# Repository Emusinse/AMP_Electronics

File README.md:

# AMP_Electronics
Custom speaker amplifier using TPA3126 IC

## Aim
This project aims to create a Class D speaker amplifier capabile of driving a set of 50W speakers. This is a personal prokect to replace a cheap 100W amps for a set of desk speakers,
Micca MB42.

## Requirements
- 2 x 50W outputs
- small form factor, smaller than 100mm x 100mm, allows cheaper PCBs
- Volume control, power switch
- AUX in, potentially RCA
- spring termiinal output
- Class D amplifier

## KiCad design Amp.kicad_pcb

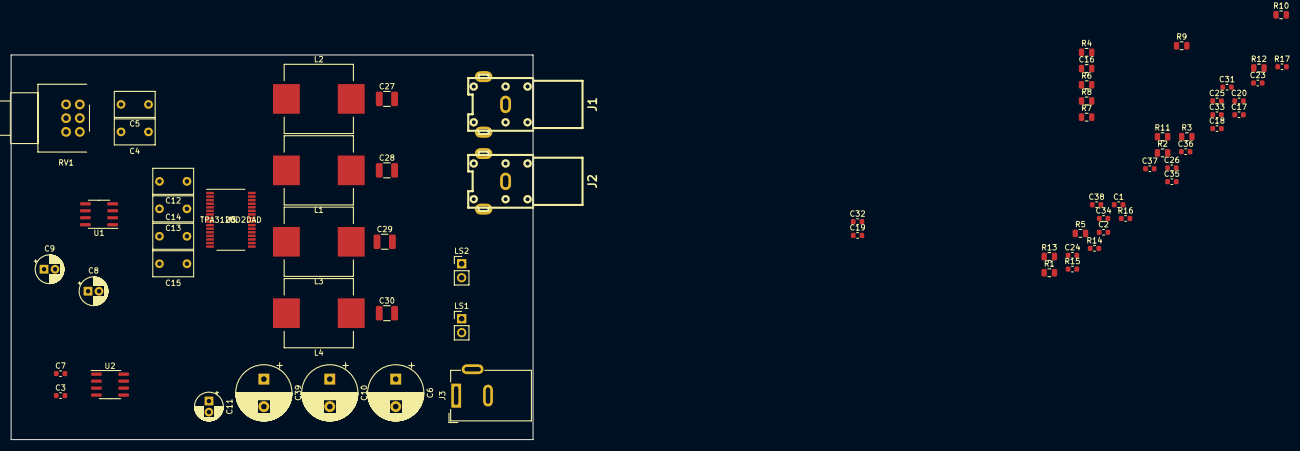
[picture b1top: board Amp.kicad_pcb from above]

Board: 2 copper layers, 95.0 x 70.0 mm, 67 parts (0 on the bottom side), 44 nets, no tracks yet.

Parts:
C1, C7, C19, C20: 100n; C_0603_1608Metric
C2, C17, C18, C31, C32, C33, C34: 1n; C_0603_1608Metric
C3: 330n; C_0603_1608Metric
C4, C5, C12, C13, C14, C15: 1u; C_Rect_L7.2mm_W4.5mm_P5.00mm_FKS2_FKP2_MKS2_MKP2
C6, C10, C39: 220uf; CP_Radial_D10.0mm_P5.00mm
C8, C9, C11: 10u; CP_Radial_D5.0mm_P2.00mm
C16: 1u; C_0805_2012Metric
C23, C24, C25, C26: 220n; C_0603_1608Metric
C27, C28, C29, C30: 680n; C_1210_3225Metric
C35, C36, C37, C38: 10n; C_0603_1608Metric
J1, J2: Conn_Coaxial; rca
J3: Barrel_Jack; BarrelJack_Wuerth_6941xx301002
L1, L2, L3, L4: 10u; L_Wuerth_WE-PD-Typ-LS_Handsoldering
LS1, LS2: L; PinHeader_1x02_P2.54mm_Vertical
R1, R2, R7, R8: 1k; R_0805_2012Metric
R3, R4, R9, R10: 47k; R_0805_2012Metric
R5, R6: 680; R_0805_2012Metric
R11, R13: 100k; R_0805_2012Metric
R12: 20k; R_0805_2012Metric
R14, R15, R16, R17: 10R; R_0603_1608Metric
RV1: R_POT_Dual-Device; Potentiometer_Bourns_PTD90_Double
U1: NE5532; SOIC-8_3.9x4.9mm_P1.27mm
U2: MC78L12_SO8; SOIC-8_3.9x4.9mm_P1.27mm
U3: TPA3126D2DAD

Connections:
+12V: C1.2, C2.1, C7.1, U1.8, U2.1
/LIN: C14.2, R10.2
/RIN: C12.2, R9.2
GNDA: C1.1, C2.2, C8.2, C9.2, C13.2, C15.2, C27.2, C28.1, C29.2, C30.1, C31.2, C32.1, C33.2, C34.1, J1.2, J2.2, R3.1, R4.1, R14.2, R15.1, R16.2, R17.1, RV1.3, RV1.6, U1.4
GNDD: C3.2, C6.2, C7.2, C10.2, C11.2, C16.2, C17.2, C18.2, C19.2, C20.2, C39.2, J3.2, R12.2, R13.1, U2.2, U2.3, U2.6, U2.7, U3.9, U3.13, U3.14, U3.15, U3.16, U3.22, U3.25, U3.28
unnamed: C4.1, R1.2
unnamed: C4.2, RV1.2
unnamed: C5.1, R2.2
unnamed: C5.2, RV1.5
unnamed: C8.1, R5.1
unnamed: C9.1, R6.1
unnamed: C6.1, C10.1, C11.1, C39.1, J3.1
unnamed: C12.1, U3.4
unnamed: C13.1, U3.5
unnamed: C14.1, U3.10
unnamed: C15.1, U3.11
unnamed: C16.1, R11.1, U3.1, U3.6, U3.7
unnamed: C23.1, L1.2, U3.29
unnamed: C23.2, U3.30
unnamed: C24.1, L2.2, U3.27
unnamed: C24.2, U3.26
unnamed: C25.1, L3.2, U3.23
unnamed: C25.2, U3.24
unnamed: C26.1, L4.2, U3.21
unnamed: C26.2, U3.20
unnamed: C27.1, C31.1, C35.1, L1.1, LS1.1
unnamed: C28.2, C32.2, C36.2, L2.1, LS1.2
unnamed: C29.1, C33.1, C37.1, L3.1, LS2.1
unnamed: C30.2, C34.2, C38.2, L4.1, LS2.2
unnamed: C35.2, R14.1
unnamed: C36.1, R15.2
unnamed: C37.2, R16.1
unnamed: C38.1, R17.2
unnamed: J1.1, RV1.1
unnamed: J2.1, RV1.4
unnamed: R1.1, R3.2, U1.3
unnamed: R2.1, R4.2, U1.5
unnamed: R5.2, R7.2, U1.2
unnamed: R6.2, R8.2, U1.6
unnamed: R7.1, R9.1, U1.1
unnamed: R8.1, R10.1, U1.7
unnamed: R11.2, R12.1, U3.8
unnamed: R13.2, U3.12
VCC: C3.1, C17.1, C18.1, C19.1, C20.1, U2.8, U3.17, U3.18, U3.19, U3.31, U3.32

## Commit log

2021-02-23 Added preliminary files
    First addition of files, schematic 95% complete, needs check over and some work on connectors. PCB not started

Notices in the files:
parts and their libraries:
Copyright 2016 Accelerated Designs. All rights reserved.
